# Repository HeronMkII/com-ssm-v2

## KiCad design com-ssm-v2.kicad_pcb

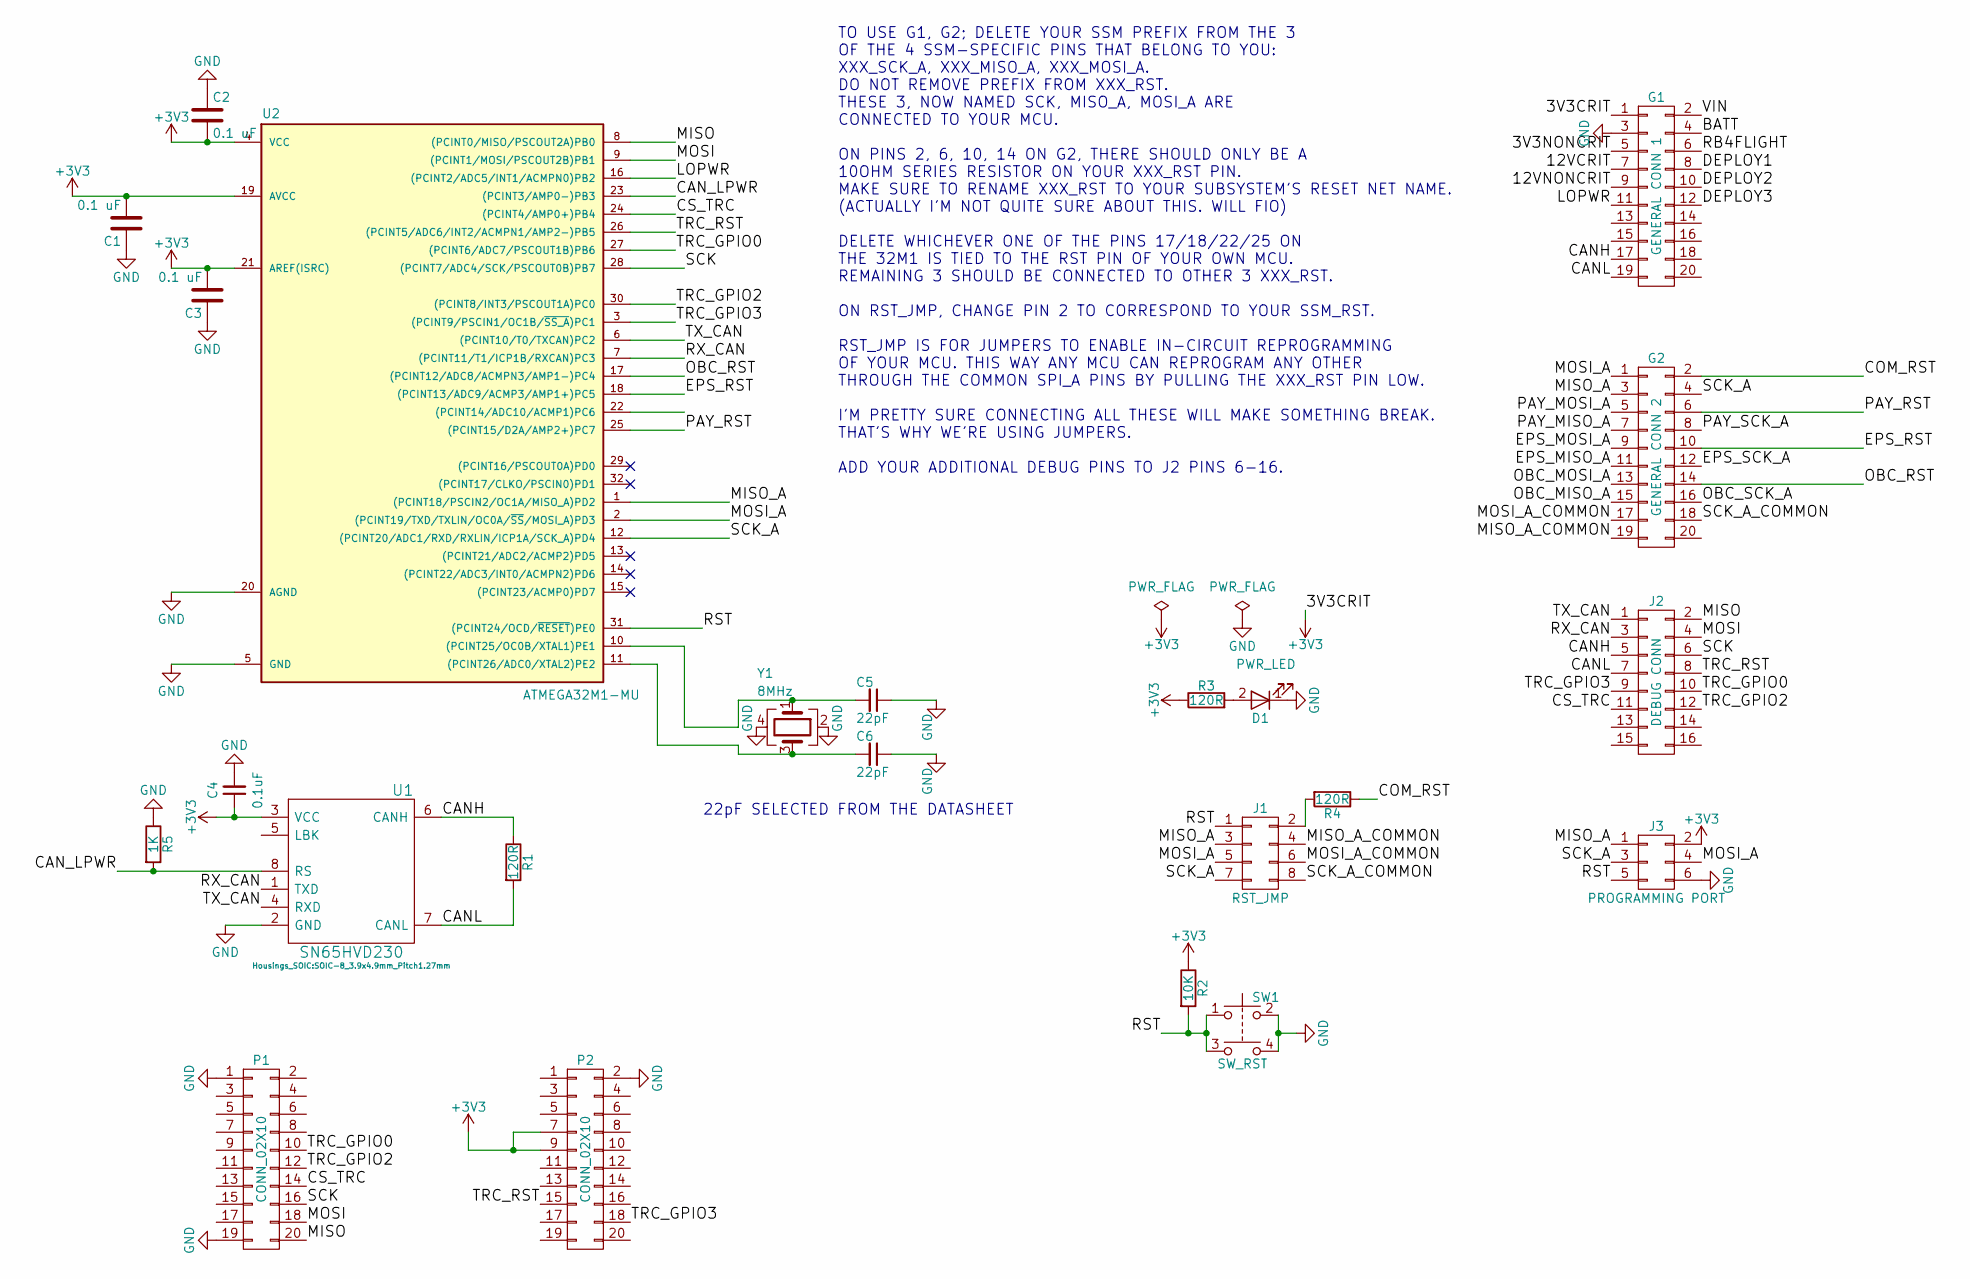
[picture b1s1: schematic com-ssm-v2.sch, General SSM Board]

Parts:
C1, C2, C3: 0.1 uF; C_0603
C4: 0.1uF; C_0603
C5, C6: 22pF; C_0603
D1: PWR_LED; LED_0603
G1: GENERAL CONN 1; Socket_Strip_Straight_2x10_Pitch2.54mm
G2: GENERAL CONN 2; Socket_Strip_Straight_2x10_Pitch2.54mm
J1: RST_JMP; Socket_Strip_Straight_2x04_Pitch2.54mm
J2: DEBUG CONN; Socket_Strip_Straight_2x08_Pitch2.54mm
J3: PROGRAMMING PORT; IDC_Header_Straight_6pins
P1, P2: CONN_02X10; Socket_Strip_Straight_2x10_Pitch1.27mm
R1, R3, R4: 120R; R_0603
R2: 10K; R_0603
R5: 1K; R_0603
SW1: SW_RST; SW_SPST_B3S-1000
U1: SN65HVD230; SOIC-8_3.9x4.9mm_Pitch1.27mm
U2: ATMEGA32M1-MU; TQFP-32_7x7mm_Pitch0.8mm
Y1: 8MHz; Crystal_SMD_Abracon_ABM3B-4pin_5.0x3.2mm

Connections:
+3V3: C1.2, C2.2, C3.2, C4.1, G1.1, J3.2, P2.7, P2.9, R2.1, R3.1, U1.3 (VCC), U2.4 (VCC), U2.19 (AVCC), U2.21 (AREF(ISRC))
/3V3NONCRIT: G1.5
/12VCRIT: G1.7
/12VNONCRIT: G1.9
/BATT: G1.4
/CANH: G1.17, J2.5, R1.1, U1.6 (CANH)
/CANL: G1.19, J2.7, R1.2, U1.7 (CANL)
/CAN_LPWR: R5.2, U1.8 (RS), U2.23 ((PCINT3/AMP0-)PB3)
/COM_RST: G2.2, R4.1
/CS_TRC: J2.11, P1.14, U2.24 ((PCINT4/AMP0+)PB4)
/DEPLOY1: G1.8
/DEPLOY2: G1.10
/DEPLOY3: G1.12
/EPS_MISO_A: G2.11
/EPS_MOSI_A: G2.9
/EPS_RST: G2.10, U2.18 ((PCINT13/ADC9/ACMP3/AMP1+)PC5)
/EPS_SCK_A: G2.12
/LOPWR: G1.11, U2.16 ((PCINT2/ADC5/INT1/ACMPN0)PB2)
/MISO: J2.2, P1.20, U2.8 ((PCINT0/MISO/PSCOUT2A)PB0)
/MISO_A: G2.3, J1.3, J3.1, U2.1 ((PCINT18/PSCIN2/OC1A/MISO_A)PD2)
/MISO_A_COMMON: G2.19, J1.4
/MOSI: J2.4, P1.18, U2.9 ((PCINT1/MOSI/PSCOUT2B)PB1)
/MOSI_A: G2.1, J1.5, J3.4, U2.2 ((PCINT19/TXD/TXLIN/OC0A/~SS~/MOSI_A)PD3)
/MOSI_A_COMMON: G2.17, J1.6
/OBC_MISO_A: G2.15
/OBC_MOSI_A: G2.13
/OBC_RST: G2.14, U2.17 ((PCINT12/ADC8/ACMPN3/AMP1-)PC4)
/OBC_SCK_A: G2.16
/PAY_MISO_A: G2.7
/PAY_MOSI_A: G2.5
/PAY_RST: G2.6, U2.25 ((PCINT15/D2A/AMP2+)PC7)
/PAY_SCK_A: G2.8
/RB4FLIGHT: G1.6
/RST: J1.1, J3.5, R2.2, SW1.1, SW1.3, U2.31 ((PCINT24/OCD/~RESET~)PE0)
/RX_CAN: J2.3, U1.1 (TXD), U2.7 ((PCINT11/T1/ICP1B/RXCAN)PC3)
/SCK: J2.6, P1.16, U2.28 ((PCINT7/ADC4/SCK/PSCOUT0B)PB7)
/SCK_A: G2.4, J1.7, J3.3, U2.12 ((PCINT20/ADC1/RXD/RXLIN/ICP1A/SCK_A)PD4)
/SCK_A_COMMON: G2.18, J1.8
/TRC_GPIO0: J2.10, P1.10, U2.27 ((PCINT6/ADC7/PSCOUT1B)PB6)
/TRC_GPIO2: J2.12, P1.12, U2.30 ((PCINT8/INT3/PSCOUT1A)PC0)
/TRC_GPIO3: J2.9, P2.18, U2.3 ((PCINT9/PSCIN1/OC1B/~SS_A~)PC1)
/TRC_RST: J2.8, P2.15, U2.26 ((PCINT5/ADC6/INT2/ACMPN1/AMP2-)PB5)
/TX_CAN: J2.1, U1.4 (RXD), U2.6 ((PCINT10/T0/TXCAN)PC2)
/VIN: G1.2
GND: C1.1, C2.1, C3.1, C4.2, C5.1, C6.1, D1.1 (K), G1.3, J3.6, P1.1, P1.19, P2.2, R5.1, SW1.2, SW1.4, U1.2 (GND), U2.5 (GND), U2.20 (AGND), Y1.2, Y1.4
unnamed: C5.2, U2.10 ((PCINT25/OC0B/XTAL1)PE1), Y1.1
unnamed: C6.2, U2.11 ((PCINT26/ADC0/XTAL2)PE2), Y1.3
unnamed: D1.2 (A), R3.2
unnamed: J1.2, R4.2

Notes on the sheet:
22pF SELECTED FROM THE DATASHEET
TO USE G1, G2; DELETE YOUR SSM PREFIX FROM THE 3 OF THE 4 SSM-SPECIFIC PINS THAT BELONG TO YOU: XXX_SCK_A, XXX_MISO_A, XXX_MOSI_A. DO NOT REMOVE PREFIX FROM XXX_RST. THESE 3, NOW NAMED SCK, MISO_A, MOSI_A ARE CONNECTED TO YOUR MCU. ON PINS 2, 6, 10, 14 ON G2, THERE SHOULD ONLY BE A 10OHM SERIES RES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

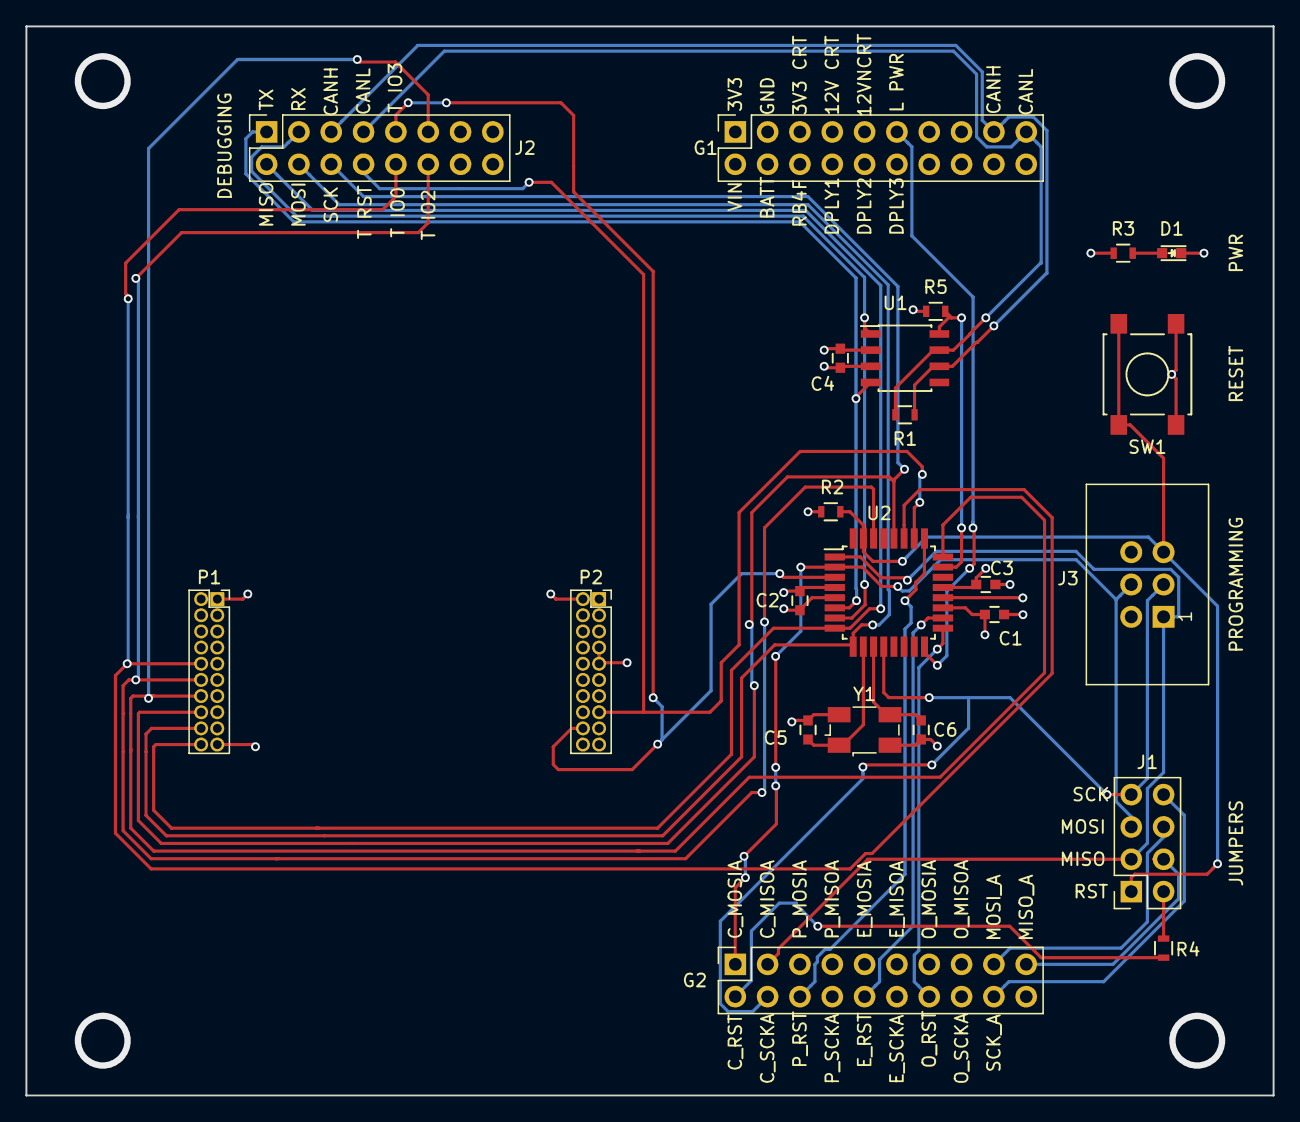
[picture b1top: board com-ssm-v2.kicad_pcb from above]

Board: 4 copper layers, 98.0 x 84.0 mm, 23 parts (0 on the bottom side), 31 nets.

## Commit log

2017-08-18 COM board with CC1120 attachment module
    p1 and p2 are for cc1120. layout should be done with care to make sure
    it fits
2017-08-19 COM board layout
    Added headers for cc1120 module. added reference files for cc1120 module
    pcb
2017-08-19 Pour power planes
2017-08-19 Fixed missing connections; DRC check passes
    Please review
2017-08-20 Mounting hole size changes.
2017-08-21 Added gerber outputs.
2017-09-02 Modified outputs for manufacture.
